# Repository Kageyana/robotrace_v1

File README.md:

# robotrace_v1

# 不具合情報
- リセット時にSDA端子がLOWに固定される.
  
  原因
  
  BNO055が通信中にリセットされBUSY状態になったから

参考

[STM32F1のI2Cの初期化でハマった](http://hima-tubusi.blogspot.com/2016/09/stm32f1i2c.html)

[STM32のI2C初期化で久しぶりにはまった](http://denshikousakusenka.blog.fc2.com/blog-entry-231.html)

[STM32のI2Cペリフェラルの初期化におけるヒント](https://www.stmcu.jp/design/document/technical_note/51180/)

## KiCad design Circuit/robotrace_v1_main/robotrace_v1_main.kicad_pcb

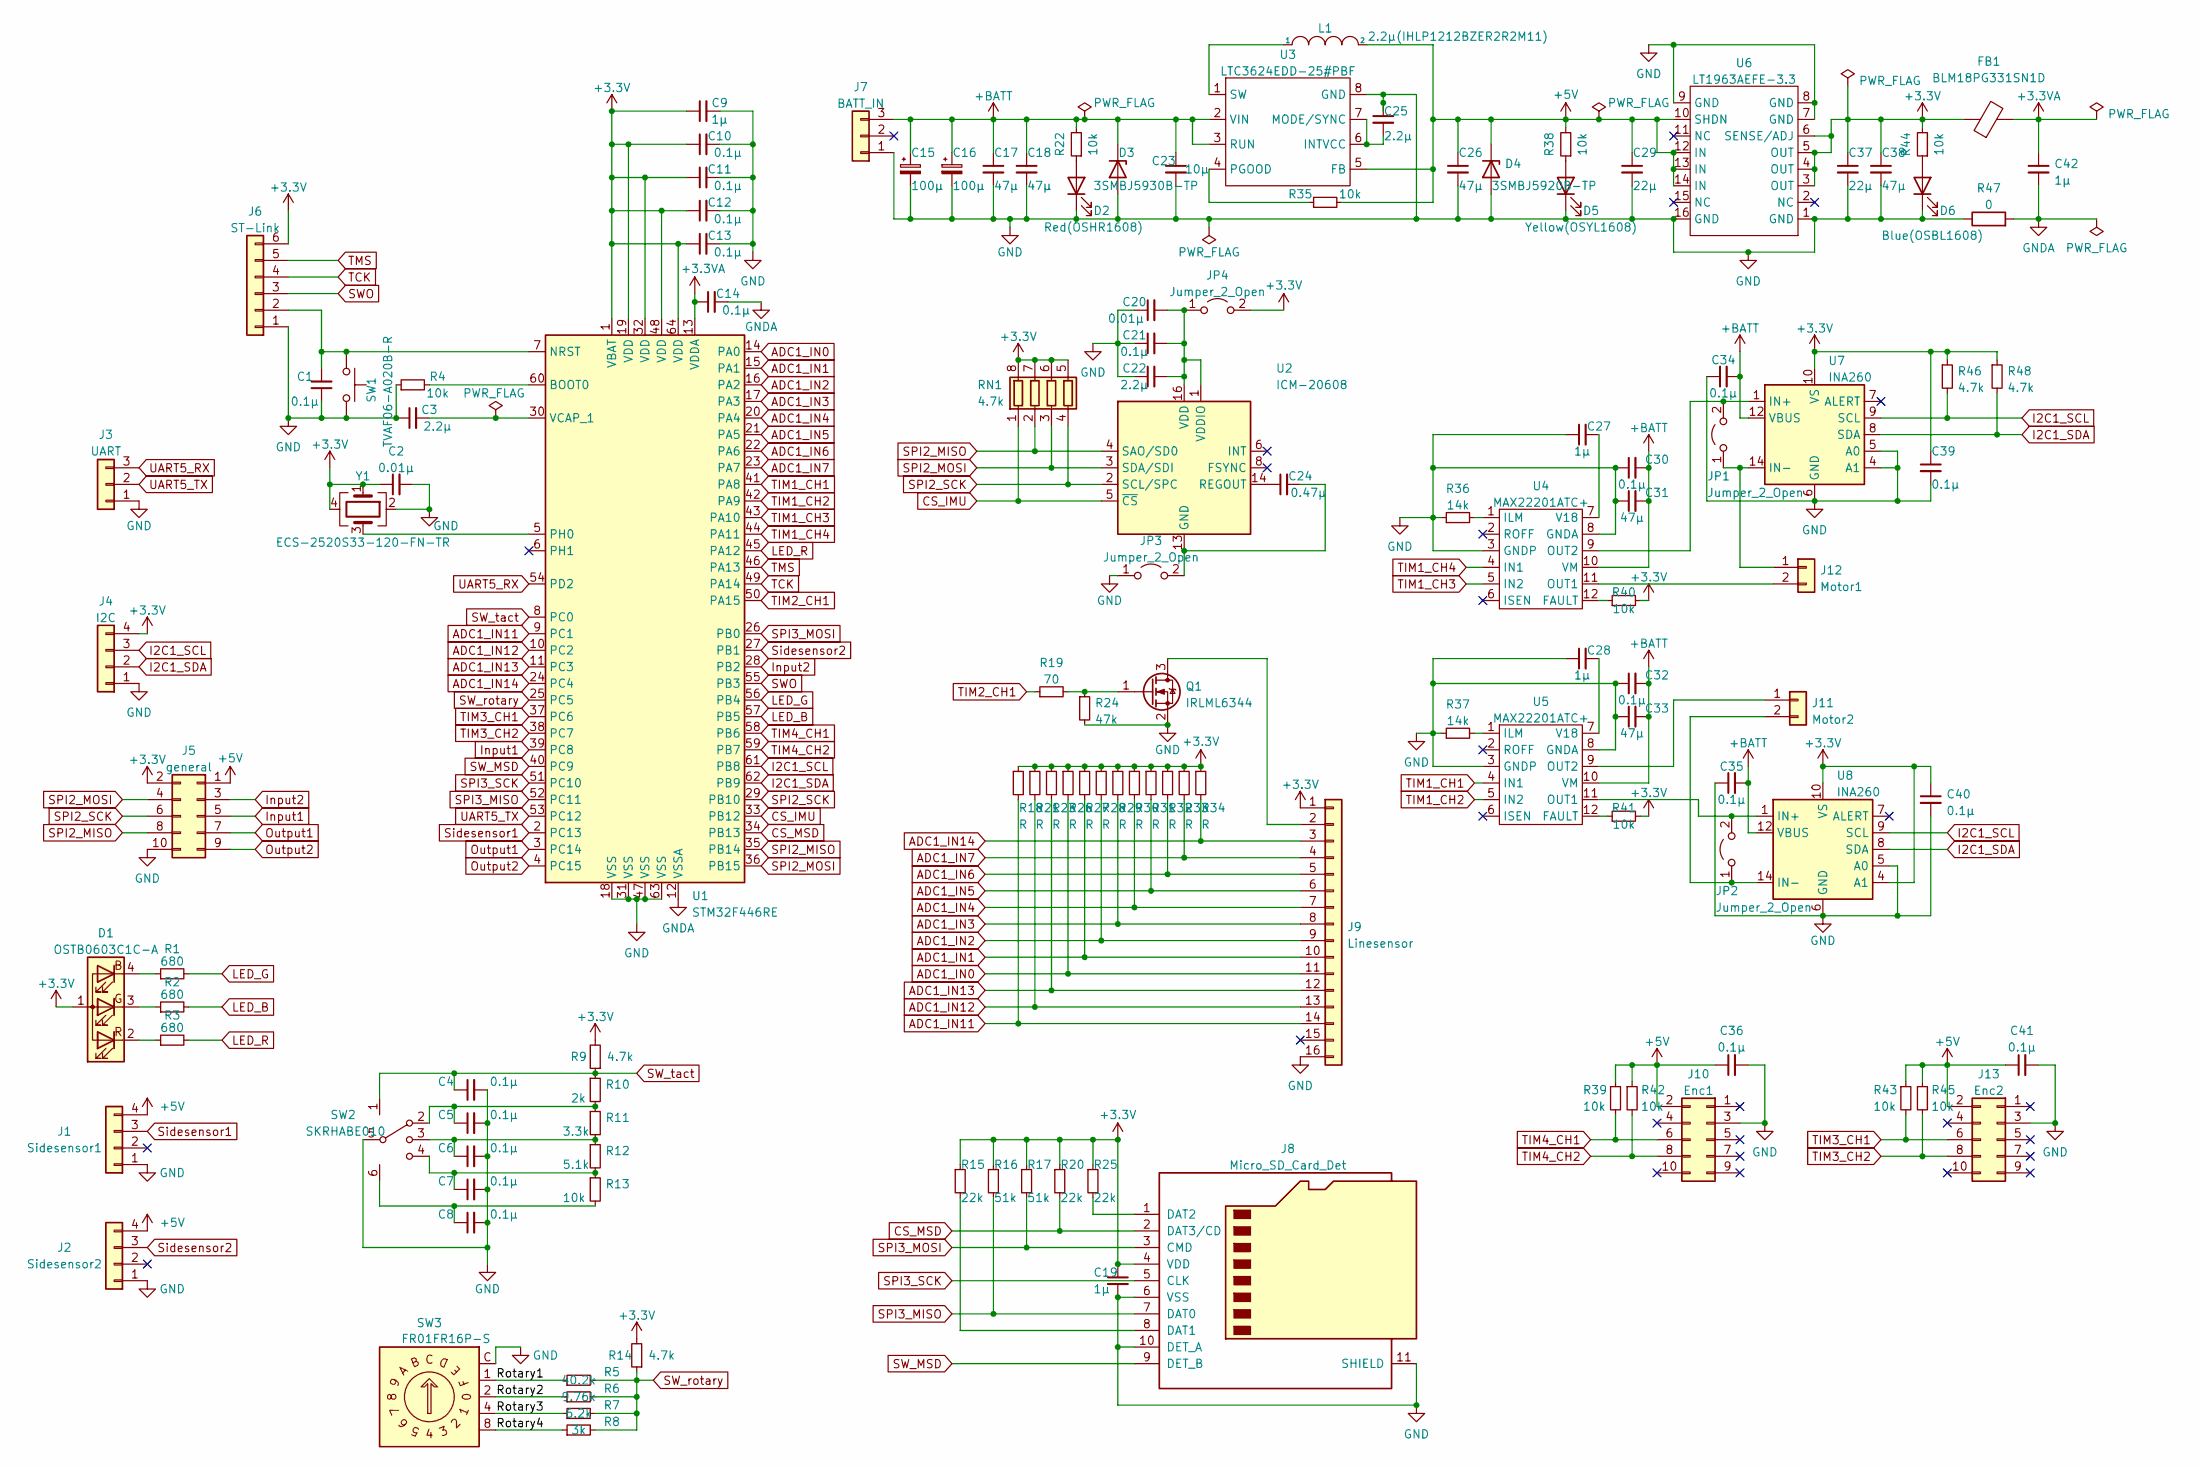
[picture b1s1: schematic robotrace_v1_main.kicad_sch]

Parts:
C1, C4, C5, C6, C7, C8, C10, C11, C12, C13, C14, C21, C30, C32, C34, C35, C36, C39, C40, C41: 0.1μ; C_0402_1005Metric_Pad0.74x0.62mm_HandSolder
C2, C20: 0.01μ; C_0402_1005Metric_Pad0.74x0.62mm_HandSolder
C3, C22, C25: 2.2μ; C_0402_1005Metric_Pad0.74x0.62mm_HandSolder
C9, C19, C27, C28, C42: 1μ; C_0402_1005Metric_Pad0.74x0.62mm_HandSolder
C15, C16: 100μ; CP_Elec_6.3x7.7
C17, C18, C26, C31, C33, C38: 47μ; C_1210_3225Metric_Pad1.33x2.70mm_HandSolder
C23: 10μ; C_0402_1005Metric_Pad0.74x0.62mm_HandSolder
C24: 0.47μ; C_0402_1005Metric_Pad0.74x0.62mm_HandSolder
C29: 22μ; C_0805_2012Metric_Pad1.18x1.45mm_HandSolder
C37: 22μ; C_0402_1005Metric_Pad0.74x0.62mm_HandSolder
D1: OSTB0603C1C-A; LED_Cree-PLCC4_2x2mm_CW
D2: Red(OSHR1608); LED_0603_1608Metric_Pad1.05x0.95mm_HandSolder
D3: 3SMBJ5930B-TP; D_SMA
D4: 3SMBJ5920B-TP; D_SMA
D5: Yellow(OSYL1608); LED_0603_1608Metric_Pad1.05x0.95mm_HandSolder
D6: Blue(OSBL1608); LED_0603_1608Metric_Pad1.05x0.95mm_HandSolder
FB1: BLM18PG331SN1D; D_0603_1608Metric
J1: Sidesensor1; Molex_FFC_1x4-1MP_P0.5mm_Horizontal
J2: Sidesensor2; Molex_FFC_1x4-1MP_P0.5mm_Horizontal
J3: UART; JST_SH_BM03B-SRSS-TB_1x03-1MP_P1.00mm_Vertical
J4: I2C; JST_SH_BM04B-SRSS-TB_1x04-1MP_P1.00mm_Vertical
J5: general; PinSocket_2x05_P1.27mm_Vertical
J6: ST-Link; JST_SH_BM06B-SRSS-TB_1x06-1MP_P1.00mm_Vertical
J7: BATT_IN; Molex_mini-SPOX_1x03_P2.54mm_Vertical
J8: Micro_SD_Card_Det; microSD_HC_Hirose_DM3AT-SF-PEJM5
J9: Linesensor; Molex_1x16_P0.50mm_Horizontal
J10: Enc1; PinSocket_2x05_P1.27mm_Vertical
J11: Motor2; Molex_mini-SPOX_1x02_P2.54mm_Vertical
J12: Motor1; Molex_mini-SPOX_1x02_P2.54mm_Vertical
J13: Enc2; PinSocket_2x05_P1.27mm_Vertical
JP1, JP2, JP3, JP4: Jumper_2_Open; SolderJumper-2_P1.3mm_Open_TrianglePad1.0x1.5mm
L1: 2.2μ(IHLP1212BZER2R2M11); L_Vishay_IHLP-1212
Q1: IRLML6344; SOT-23
R1, R2, R3: 680; R_0603_1608Metric
R4, R13, R22, R35, R38, R39, R40, R41, R42, R43, R44, R45: 10k; R_0603_1608Metric
R5: 40.2k; R_0603_1608Metric
R6: 9.76k; R_0603_1608Metric
R7: 6.2k; R_0603_1608Metric
R8: 3k; R_0603_1608Metric
R9, R14, R46, R48: 4.7k; R_0603_1608Metric
R10: 2k; R_0603_1608Metric
R11: 3.3k; R_0603_1608Metric
R12: 5.1k; R_0603_1608Metric
R15, R20, R25: 22k; R_0603_1608Metric
R16, R17: 51k; R_0603_1608Metric
R18, R21, R23, R26, R27, R28, R29, R30, R31, R32, R33, R34: R; R_0603_1608Metric
R19: 70; R_0603_1608Metric
R24: 47k; R_0603_1608Metric
R36, R37: 14k; R_0603_1608Metric
R47: 0; R_0603_1608Metric
RN1: 4.7k; R_Array_Convex_4x0402
SW1: TVAF06-A020B-R; SW_Push_SPST_NO_Alps_SKRK
SW2: SKRHABE010; SKRHAAE010
SW3: FR01FR16P-S
U1: STM32F446RE; LQFP-64_10x10mm_P0.5mm
U2: ICM-20608; LGA-16_3x3mm_P0.5mm_LayoutBorder3x5y
U3: LTC3624EDD-25#PBF; DFN-8-1EP_3x3mm_P0.5mm_EP1.65x2.38mm
U4, U5: MAX22201ATC+; DFN-12-1EP_3x3mm_P0.5mm_EP1.6x2.5mm
U6: LT1963AEFE-3.3; HTSSOP-16-1EP_4.4x5mm_P0.65mm_EP3.4x5mm
U7, U8: INA260; TSSOP-16_4.4x5mm_P0.65mm
Y1: ECS-2520S33-120-FN-TR; Crystal_SMD_EuroQuartz_MT-4Pin_3.2x2.5mm

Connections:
+3.3VA: C14.1, C42.1, FB1.2, U1.13 (VDDA)
+3V3: C2.1, C9.1, C10.1, C11.1, C12.1, C13.1, C19.1, C37.1, C38.1, C39.1, C40.1, D1.1 (A), FB1.1, J4.4, J5.2, J6.6, J8.4 (VDD), J9.1, JP4.2 (B), R9.2, R14.2, R15.1, R16.1, R17.1, R18.1, R20.1, R21.1, R23.1, R25.1, R26.1, R27.1, R28.1, R29.1, R30.1, R31.1, R32.1, R33.1, R34.1, R40.2, R41.2, R44.2, R46.1, R48.1, RN1.5 (R4.2), RN1.6 (R3.2), RN1.7 (R2.2), RN1.8 (R1.2), U1.1 (VBAT), U1.19 (VDD), U1.32 (VDD), U1.48 (VDD), U1.64 (VDD), U6.3 (OUT), U6.4 (OUT), U6.5 (OUT), U6.6 (SENSE/ADJ), U7.10 (VS), U8.4 (A1), U8.10 (VS), Y1.1, Y1.4
+5V: C26.1, C29.1, C36.1, C41.1, D4.1 (K), J1.4, J2.4, J5.1, J10.2, J13.2, L1.2, R35.2, R38.2, R39.1, R42.1, R43.1, R45.1, U3.5 (FB), U6.10 (SHDN), U6.12 (IN), U6.13 (IN), U6.14 (IN)
+BATT: C15.1, C16.1, C17.1, C18.1, C23.1, C30.2, C31.2, C32.2, C33.2, C34.2, C35.2, D3.1 (K), J7.3, R22.2, U3.2 (VIN), U3.3 (RUN), U4.10 (VM), U5.10 (VM), U7.12 (VBUS), U8.12 (VBUS)
/Rotary1: R5.1, SW3.1
/Rotary2: R6.1, SW3.2
/Rotary3: R7.1, SW3.4
/Rotary4: R8.1, SW3.8
ADC1_IN0: J9.11, R26.2, U1.14 (PA0)
ADC1_IN1: J9.10, R27.2, U1.15 (PA1)
ADC1_IN2: J9.9, R28.2, U1.16 (PA2)
ADC1_IN3: J9.8, R29.2, U1.17 (PA3)
ADC1_IN4: J9.7, R30.2, U1.20 (PA4)
ADC1_IN5: J9.6, R31.2, U1.21 (PA5)
ADC1_IN6: J9.5, R32.2, U1.22 (PA6)
ADC1_IN7: J9.4, R33.2, U1.23 (PA7)
ADC1_IN11: J9.14, R18.2, U1.9 (PC1)
ADC1_IN12: J9.13, R21.2, U1.10 (PC2)
ADC1_IN13: J9.12, R23.2, U1.11 (PC3)
ADC1_IN14: J9.3, R34.2, U1.24 (PC4)
CS_IMU: RN1.1 (R1.1), U1.33 (PB12), U2.5 (~CS)
CS_MSD: J8.2 (DAT3/CD), R20.2, U1.34 (PB13)
GNDA: C14.2, C42.2, R47.2, U1.12 (VSSA)
I2C1_SCL: J4.3, R46.2, U1.61 (PB8), U7.9 (SCL), U8.9 (SCL)
I2C1_SDA: J4.2, R48.2, U1.62 (PB9), U7.8 (SDA), U8.8 (SDA)
Input1: J5.5, U1.39 (PC8)
Input2: J5.3, U1.28 (PB2)
LED1: R1.2, U1.56 (PB4)
LED2: R2.2, U1.57 (PB5)
LED3: R3.2, U1.45 (PA12)
unnamed: C1.2, J6.2, SW1.1, U1.7 (NRST)
unnamed: C3.2, U1.30 (VCAP_1)
unnamed: C5.1, R10.2, R11.1, SW2.2
unnamed: C6.1, R11.2, R12.1, SW2.3
unnamed: C7.1, R12.2, R13.1, SW2.4
unnamed: C20.2, C21.2, C22.2, JP4.1 (A), U2.1 (VDDIO), U2.16 (VDD)
unnamed: C24.1, U2.14 (REGOUT)
unnamed: C24.2, JP3.2 (B), U2.9 (GND), U2.10 (GND), U2.11 (GND), U2.12 (GND), U2.13 (GND), U2.15 (GND)
unnamed: C25.2, U3.6 (INTVCC), U3.7 (MODE/SYNC)
unnamed: C27.2, U4.7 (V18)
unnamed: C28.2, U5.7 (V18)
unnamed: D1.2 (RK), R3.1
unnamed: D1.3 (GK), R2.1
unnamed: D1.4 (BK), R1.1
unnamed: D2.2 (A), R22.1
unnamed: D5.2 (A), R38.1
unnamed: D6.2 (A), R44.1
unnamed: J8.1 (DAT2), R25.2
unnamed: J8.8 (DAT1), R15.2
unnamed: J9.2, Q1.3 (D)
unnamed: J11.1, U5.9 (OUT2)
unnamed: J11.2, JP2.1 (A), U8.14 (IN-), U8.15 (IN-), U8.16 (IN-)
unnamed: J12.1, JP1.1 (A), U7.14 (IN-), U7.15 (IN-), U7.16 (IN-)
unnamed: J12.2, U4.11 (OUT1)
unnamed: JP1.2 (B), U4.9 (OUT2), U7.1 (IN+), U7.2 (IN+), U7.3 (IN+)
unnamed: JP2.2 (B), U5.11 (OUT1), U8.1 (IN+), U8.2 (IN+), U8.3 (IN+)
unnamed: L1.1, U3.1 (SW)
unnamed: Q1.1 (G), R19.2, R24.1
unnamed: R4.2, U1.60 (BOOT0)
unnamed: R35.1, U3.4 (PGOOD)
unnamed: R36.2, U4.1 (ILM)
unnamed: R37.2, U5.1 (ILM)
unnamed: R40.1, U4.12 (FAULT)
unnamed: R41.1, U5.12 (FAULT)
unnamed: U1.5 (PH0), Y1.3
Output1: J5.7, U1.3 (PC14)
Output2: J5.9, U1.4 (PC15)
SPI2_MISO: J5.8, RN1.2 (R2.1), U1.35 (PB14), U2.4 (SAO/SD0)
SPI2_MOSI: J5.4, RN1.3 (R3.1), U1.36 (PB15), U2.3 (SDA/SDI)
SPI2_SCK: J5.6, RN1.4 (R4.1), U1.29 (PB10), U2.2 (SCL/SPC)
SPI3_MISO: J8.7 (DAT0), R16.2, U1.52 (PC11)
SPI3_MOSI: J8.3 (CMD), R17.2, U1.26 (PB0)
SPI3_SCK: J8.5 (CLK), U1.51 (PC10)
SWO: J6.3, U1.55 (PB3)
SW_MSD: J8.9 (DET_B), U1.40 (PC9)
SW_rotary: R5.2, R6.2, R7.2, R8.2, R14.1, U1.25 (PC5)
SW_tact: C4.1, R9.1, R10.1, SW2.1, U1.8 (PC0)
Sidesensor1: J1.3, U1.2 (PC13)
Sidesensor2: J2.3, U1.27 (PB1)
TCK: J6.4, U1.49 (PA14)
TIM1_CH1: U1.41 (PA8), U5.4 (IN1)
TIM1_CH2: U1.42 (PA9), U5.5 (IN2)
TIM1_CH3: U1.43 (PA10), U4.5 (IN2)
TIM1_CH4: U1.44 (PA11), U4.4 (IN1)
TIM2_CH1: R19.1, U1.50 (PA15)
TIM4_CH1: J10.6, R39.2, U1.58 (PB6)
TIM4_CH2: J10.8, R42.2, U1.59 (PB7)
TIM5_CH1: J13.6, R43.2, U1.37 (PC6)
TIM5_CH2: J13.8, R45.2, U1.38 (PC7)
TMS: J6.5, U1.46 (PA13)
UART5_RX: J3.3, U1.54 (PD2)
UART5_TX: J3.2, U1.53 (PC12)

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
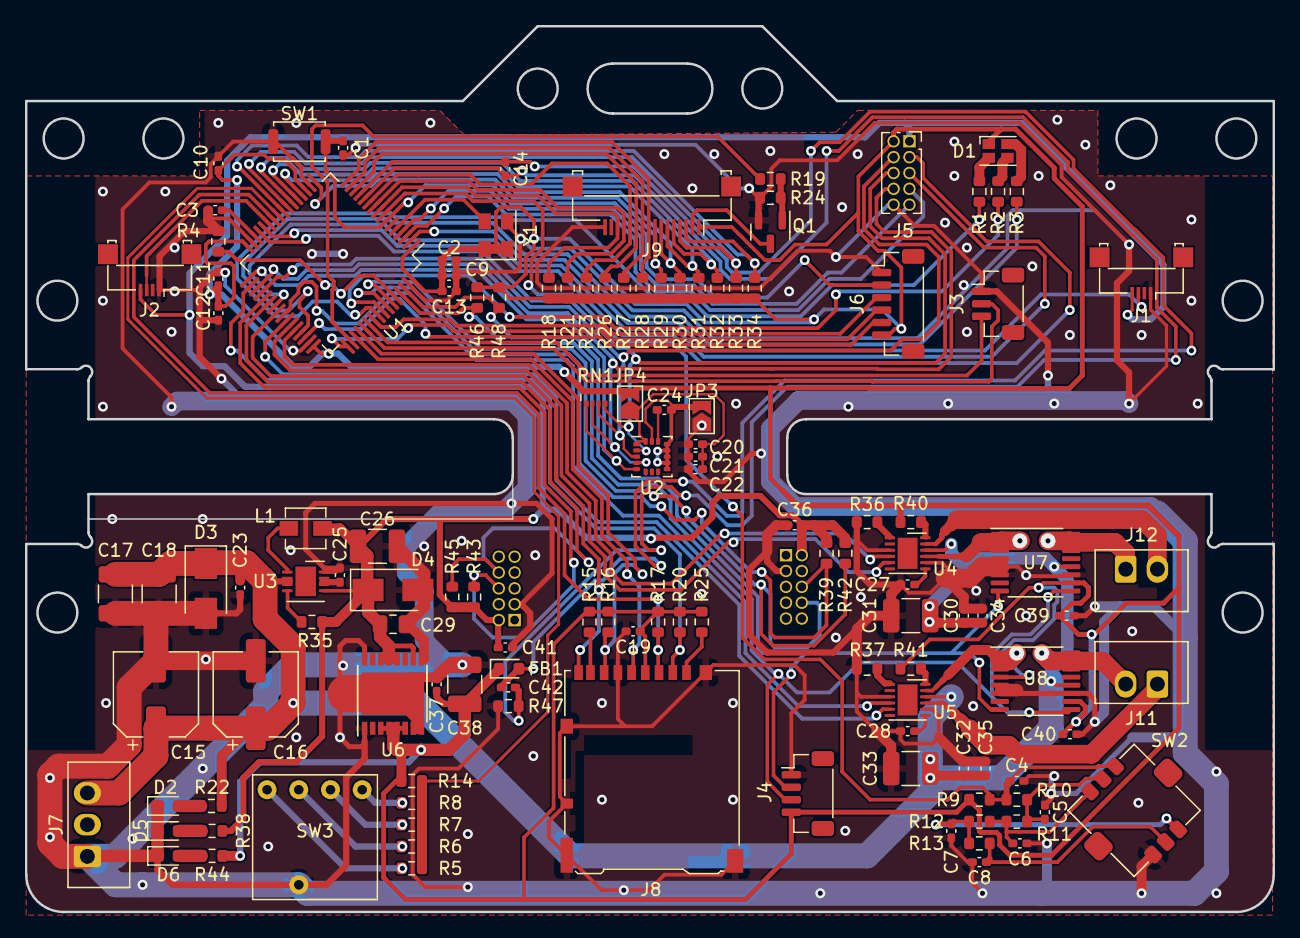
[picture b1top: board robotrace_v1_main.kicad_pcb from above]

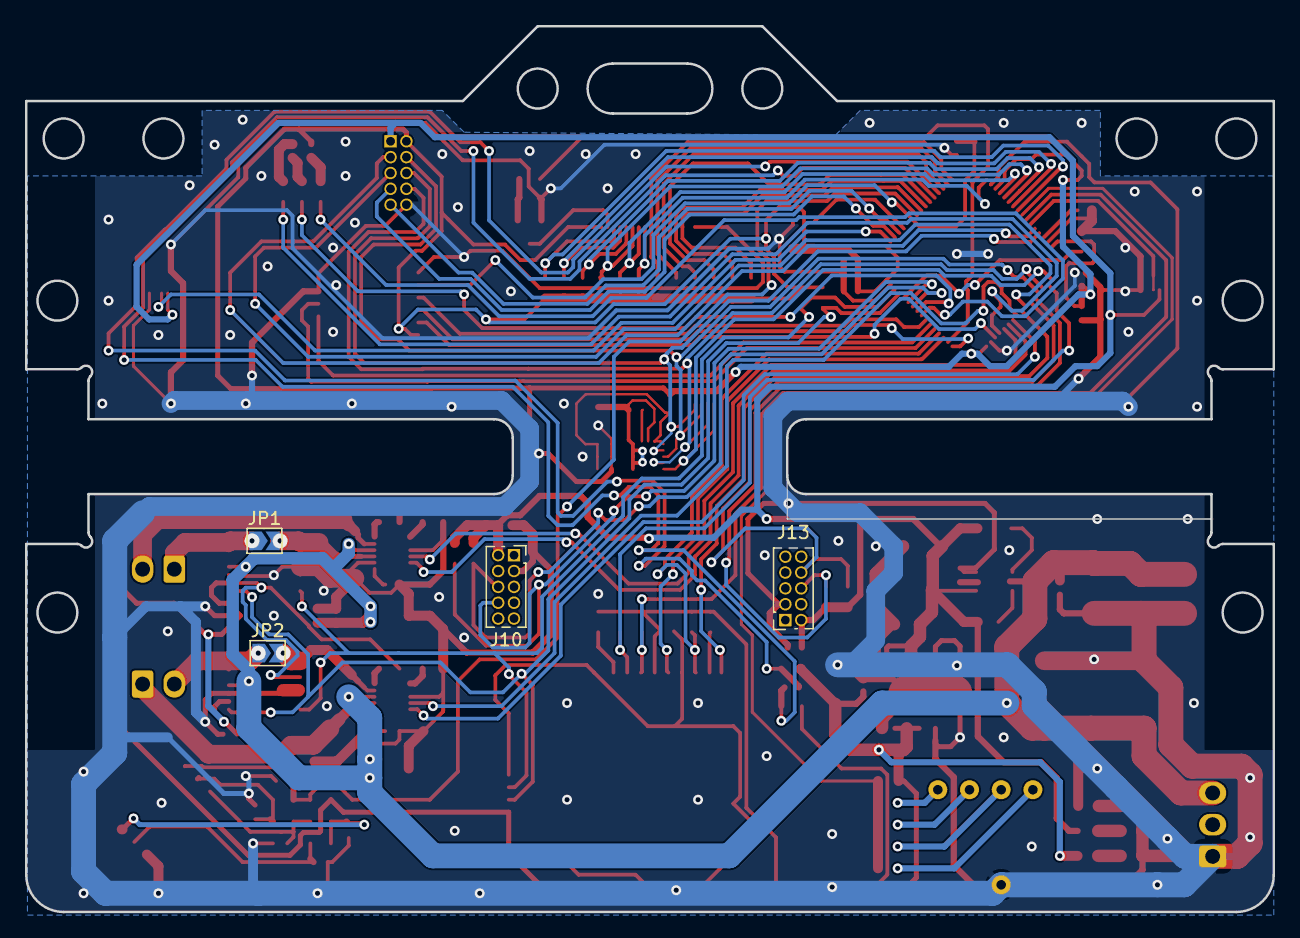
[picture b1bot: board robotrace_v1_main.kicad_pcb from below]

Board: 2 copper layers, 100.0 x 71.0 mm, 129 parts (4 on the bottom side), 94 nets.

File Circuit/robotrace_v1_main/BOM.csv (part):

"Source:","F:\Dropbox\Document\CAD\Ki_cad\robotrace_v1_main\robotrace_v1_main.kicad_sch"
"Date:","2023/03/18 18:05:15"
"Tool:","Eeschema (7.0.0)"
"Generator:","C:\Program Files\KiCad\6.0\bin\scripting\plugins/bom_csv_grouped_by_value_with_fp.py"
"Component Count:","129"
"Ref","Qnty","Value","Cmp name","Footprint","Description","Vendor"
"C1, C4, C5, C6, C7, C8, C10, C11, C12, C13, C14, C21, C30, C32, C34, C35, C36, C39, C40, C41, ","20","0.1μ","C_Small","Capacitor_SMD:C_0402_1005Metric_Pad0.74x0.62mm_HandSolder","Unpolarized capacitor, small symbol",""
"C2, C20, ","2","0.01μ","C_Small","Capacitor_SMD:C_0402_1005Metric_Pad0.74x0.62mm_HandSolder","Unpolarized capacitor, small symbol",""
"C3, C22, C25, ","3","2.2μ","C_Small","Capacitor_SMD:C_0402_1005Metric_Pad0.74x0.62mm_HandSolder","Unpolarized capacitor, small symbol",""
"C9, C19, C27, C28, C42, ","5","1μ","C_Small","Capacitor_SMD:C_0402_1005Metric_Pad0.74x0.62mm_HandSolder","Unpolarized capacitor, small symbol",""
"C15, C16, ","2","100μ","C_Polarized_Small","Capacitor_SMD:CP_Elec_6.3x7.7","Polarized capacitor, small symbol",""
"C17, C18, C26, C31, C33, C38, ","6","47μ","C_Small","Capacitor_SMD:C_1210_3225Metric_Pad1.33x2.70mm_HandSolder","Unpolarized capacitor, small symbol",""
"C23, ","1","10μ","C_Small","Capacitor_SMD:C_0402_1005Metric_Pad0.74x0.62mm_HandSolder","Unpolarized capacitor, small symbol",""
"C24, ","1","0.47μ","C_Small","Capacitor_SMD:C_0402_1005Metric_Pad0.74x0.62mm_HandSolder","Unpolarized capacitor, small symbol",""
"C29, ","1","22μ","C_Small","Capacitor_SMD:C_0805_2012Metric_Pad1.18x1.45mm_HandSolder","Unpolarized capacitor, small symbol",""
"C37, ","1","22μ","C_Small","Capacitor_SMD:C_0402_1005Metric_Pad0.74x0.62mm_HandSolder","Unpolarized capacitor, small symbol",""
"D1, ","1","OSTB0603C1C-A","LED_ARGB","LED_SMD:LED_Cree-PLCC4_2x2mm_CW","RGB LED, anode/red/green/blue",""
"D2, ","1","Red(OSHR1608)","LED","LED_SMD:LED_0603_1608Metric_Pad1.05x0.95mm_HandSolder","Light emitting diode",""
"D3, ","1","3SMBJ5930B-TP","D_Zener","Diode_SMD:D_SMA","Zener diode",""
"D4, ","1","3SMBJ5920B-TP","D_Zener","Diode_SMD:D_SMA","Zener diode",""
"D5, ","1","Yellow(OSYL1608)","LED","LED_SMD:LED_0603_1608Metric_Pad1.05x0.95mm_HandSolder","Light emitting diode",""
"D6, ","1","Blue(OSBL1608)","LED","LED_SMD:LED_0603_1608Metric_Pad1.05x0.95mm_HandSolder","Light emitting diode",""
"FB1, ","1","BLM18PG331SN1D","FerriteBead","Diode_SMD:D_0603_1608Metric","Ferrite bead",""
"J1, ","1","Sidesensor1","Conn_01x04","robot_contest:Molex_FFC_1x4-1MP_P0.5mm_Horizontal","Generic connector, single row, 01x04, script generated (kicad-library-utils/schlib/autogen/connector/)",""
"J2, ","1","Sidesensor2","Conn_01x04","robot_contest:Molex_FFC_1x4-1MP_P0.5mm_Horizontal","Generic connector, single row, 01x04, script generated (kicad-library-utils/schlib/autogen/connector/)",""
"J3, ","1","UART","Conn_01x03","Connector_JST:JST_SH_BM03B-SRSS-TB_1x03-1MP_P1.00mm_Vertical","Generic connector, single row, 01x03, script generated (kicad-library-utils/schlib/autogen/connector/)",""
"J4, ","1","I2C","Conn_01x04","Connector_JST:JST_SH_BM04B-SRSS-TB_1x04-1MP_P1.00mm_Vertical","Generic connector, single row, 01x04, script generated (kicad-library-utils/schlib/autogen/connector/)",""
"J5, ","1","general","Conn_02x05_Odd_Even","Connector_PinSocket_1.27mm:PinSocket_2x05_P1.27mm_Vertical","Generic connector, double row, 02x05, odd/even pin numbering scheme (row 1 odd numbers, row 2 even numbers), script generated (kicad-library-utils/schlib/autogen/connector/)",""
"J6, ","1","ST-Link","Conn_01x06","Connector_JST:JST_SH_BM06B-SRSS-TB_1x06-1MP_P1.00mm_Vertical","Generic connector, single row, 01x06, script generated (kicad-library-utils/schlib/autogen/connector/)",""
"J7, ","1","BATT_IN","Conn_01x03","robot_contest:Molex_mini-SPOX_1x03_P2.54mm_Vertical","Generic connector, single row, 01x03, script generated (kicad-library-utils/schlib/autogen/connector/)",""
"J8, ","1","Micro_SD_Card_Det","Micro_SD_Card_Det","Connector_Card:microSD_HC_Hirose_DM3AT-SF-PEJM5","Micro SD Card Socket with card detection pins",""
"J9, ","1","Linesensor","Conn_01x16","robot_contest:Molex_1x16_P0.50mm_Horizontal","Generic connector, single row, 01x16, script generated (kicad-library-utils/schlib/autogen/connector/)",""
"J10, ","1","Enc1","Conn_02x05_Odd_Even","Connector_PinSocket_1.27mm:PinSocket_2x05_P1.27mm_Vertical","Generic connector, double row, 02x05, odd/even pin numbering scheme (row 1 odd numbers, row 2 even numbers), script generated (kicad-library-utils/schlib/autogen/connector/)",""
"J11, ","1","Motor2","Conn_01x02","robot_contest:Molex_mini-SPOX_1x02_P2.54mm_Vertical","Generic connector, single row, 01x02, script generated (kicad-library-utils/schlib/autogen/connector/)",""
"J12, ","1","Motor1","Conn_01x02","robot_contest:Molex_mini-SPOX_1x02_P2.54mm_Vertical","Generic connector, single row, 01x02, script generated (kicad-library-utils/schlib/autogen/connector/)",""
"J13, ","1","Enc2","Conn_02x05_Odd_Even","Connector_PinSocket_1.27mm:PinSocket_2x05_P1.27mm_Vertical","Generic connector, double row, 02x05, odd/even pin numbering scheme (row 1 odd numbers, row 2 even numbers), script generated (kicad-library-utils/schlib/autogen/connector/)",""
"JP1, JP2, JP3, JP4, ","4","Jumper_2_Open","Jumper_2_Open","Jumper:SolderJumper-2_P1.3mm_Open_TrianglePad1.0x1.5mm","Jumper, 2-pole, open",""
"L1, ","1","2.2μ(IHLP1212BZER2R2M11)","INDUCTOR","Inductor_SMD:L_Vishay_IHLP-1212","Inductor symbol for simulation only",""
"Q1, ","1","IRLML6344","Q_NMOS_GSD","Package_TO_SOT_SMD:SOT-23","N-MOSFET transistor, gate/source/drain",""
"R1, R2, R3, ","3","680","R_Small","Resistor_SMD:R_0603_1608Metric","Resistor, small symbol",""
"R4, R13, R22, R35, R38, R39, R40, R41, R42, R43, R44, R45, ","12","10k","R_Small","Resistor_SMD:R_0603_1608Metric","Resistor, small symbol",""
"R5, ","1","40.2k","R_Small","Resistor_SMD:R_0603_1608Metric","Resistor, small symbol",""
"R6, ","1","9.76k","R_Small","Resistor_SMD:R_0603_1608Metric","Resistor, small symbol",""
"R7, ","1","6.2k","R_Small","Resistor_SMD:R_0603_1608Metric","Resistor, small symbol",""
"R8, ","1","3k","R_Small","Resistor_SMD:R_0603_1608Metric","Resistor, small symbol",""
"R9, R14, R46, R48, ","4","4.7k","R_Small","Resistor_SMD:R_0603_1608Metric","Resistor, small symbol",""
"R10, ","1","2k","R_Small","Resistor_SMD:R_0603_1608Metric","Resistor, small symbol",""
"R11, ","1","3.3k","R_Small","Resistor_SMD:R_0603_1608Metric","Resistor, small symbol",""
"R12, ","1","5.1k","R_Small","Resistor_SMD:R_0603_1608Metric","Resistor, small symbol",""
"R15, R20, R25, ","3","22k","R_Small","Resistor_SMD:R_0603_1608Metric","Resistor, small symbol",""
"R16, R17, ","2","51k","R_Small","Resistor_SMD:R_0603_1608Metric","Resistor, small symbol",""
"R18, R21, R23, R26, R27, R28, R29, R30, R31, R32, R33, R34, ","12","R","R_Small","Resistor_SMD:R_0603_1608Metric","Resistor, small symbol",""
"R19, ","1","70","R_Small","Resistor_SMD:R_0603_1608Metric","Resistor, small symbol",""
"R24, ","1","47k","R_Small","Resistor_SMD:R_0603_1608Metric","Resistor, small symbol",""
"R36, R37, ","2","14k","R_Small","Resistor_SMD:R_0603_1608Metric","Resistor, small symbol",""
"R47, ","1","0","R","Resistor_SMD:R_0603_1608Metric","Resistor",""
"RN1, ","1","4.7k","R_Pack04","Resistor_SMD:R_Array_Convex_4x0402","4 resistor network, parallel topology",""
"SW1, ","1","TVAF06-A020B-R","SW_Push","Button_Switch_SMD:SW_Push_SPST_NO_Alps_SKRK","Push button switch, generic, two pins",""
"SW2, ","1","SKRHABE010","SW_SP3T","robot_contest:SKRHAAE010","Switch, three position, single pole triple throw, 3 position switch, SP3T",""
"SW3, ","1","FR01FR16P-S","SW_Coded_SH-7050","robot_contest:FR01FR16P-S","Rotary switch, 4-bit encoding, 16 positions, Real code",""
"U1, ","1","STM32F446RE","STM32F446RCTx","Package_QFP:LQFP-64_10x10mm_P0.5mm","ARM Cortex-M4 MCU, 256KB flash, 128KB RAM, 180MHz, 1.8-3.6V, 50 GPIO, LQFP-64",""
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
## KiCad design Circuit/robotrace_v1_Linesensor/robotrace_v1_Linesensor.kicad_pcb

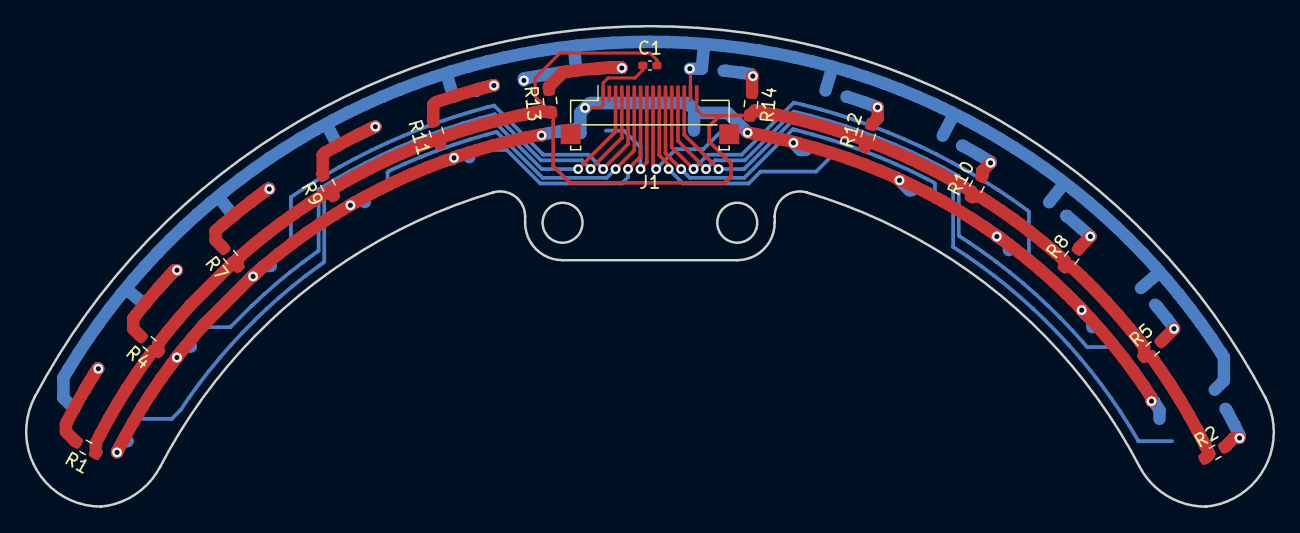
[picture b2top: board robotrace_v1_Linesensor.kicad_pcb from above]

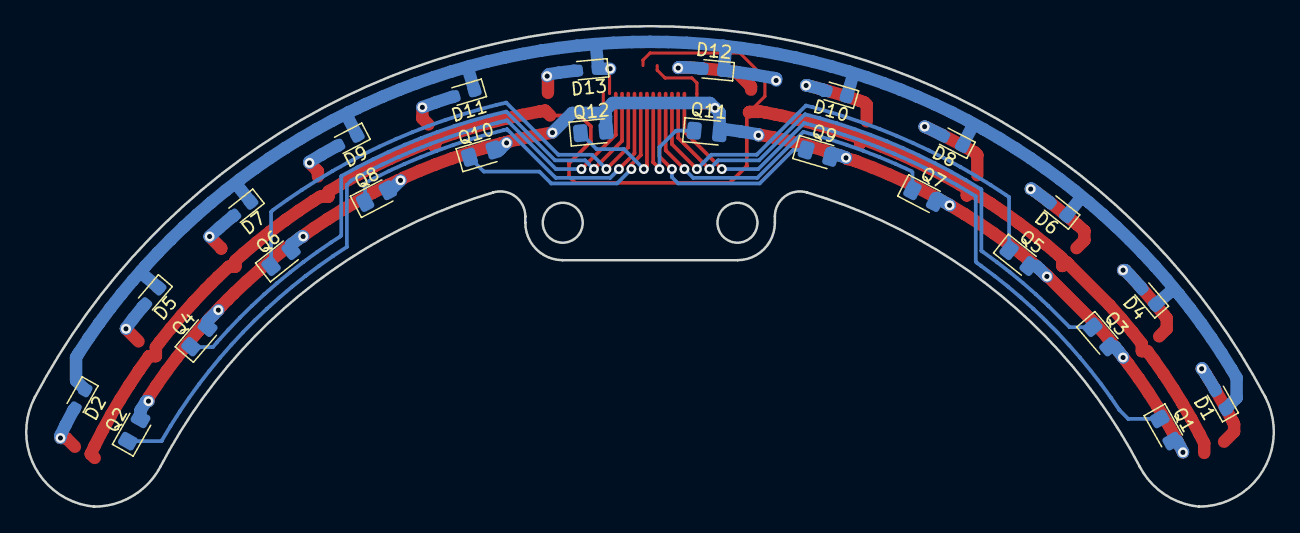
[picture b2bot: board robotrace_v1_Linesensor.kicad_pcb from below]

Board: 2 copper layers, 100.0 x 38.5 mm, 38 parts (24 on the bottom side), 27 nets.

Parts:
C1: 1μ; C_0402_1005Metric_Pad0.74x0.62mm_HandSolder
D1, D2, D4, D5, D6, D7, D8, D9, D10, D11, D12, D13: SIR19-21C/TR8; LED_0603_1608Metric_Pad1.05x0.95mm_HandSolder
J1: FFC_16P; Molex_1x16_P0.50mm_Horizontal
Q1, Q2, Q3, Q4, Q5, Q6, Q7, Q8, Q9, Q10, Q11, Q12: TEMT7100X01; LED_0805_2012Metric_Pad1.15x1.40mm_HandSolder
R1, R2, R4, R5, R7, R8, R9, R10, R11, R12, R13, R14: 100; R_0603_1608Metric_Pad0.98x0.95mm_HandSolder

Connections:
+3V3: C1.1, J1.16, R1.1, R2.1, R4.1, R5.1, R7.1, R8.1, R9.1, R10.1, R11.1, R12.1, R13.1, R14.1
GND1: C1.2, J1.1, Q1.2 (E), Q2.2 (E), Q3.2 (E), Q4.2 (E), Q5.2 (E), Q6.2 (E), Q7.2 (E), Q8.2 (E), Q9.2 (E), Q10.2 (E), Q11.2 (E), Q12.2 (E)
unnamed: D1.1 (K), D2.1 (K), D4.1 (K), D5.1 (K), D6.1 (K), D7.1 (K), D8.1 (K), D9.1 (K), D10.1 (K), D11.1 (K), D12.1 (K), D13.1 (K), J1.15
unnamed: D1.2 (A), R1.2
unnamed: D2.2 (A), R2.2
unnamed: D4.2 (A), R4.2
unnamed: D5.2 (A), R5.2
unnamed: D6.2 (A), R7.2
unnamed: D7.2 (A), R8.2
unnamed: D8.2 (A), R9.2
unnamed: D9.2 (A), R10.2
unnamed: D10.2 (A), R11.2
unnamed: D11.2 (A), R12.2
unnamed: D12.2 (A), R13.2
unnamed: D13.2 (A), R14.2
unnamed: J1.3, Q1.1 (C)
unnamed: J1.4, Q3.1 (C)
unnamed: J1.5, Q5.1 (C)
unnamed: J1.6, Q7.1 (C)
unnamed: J1.7, Q9.1 (C)
unnamed: J1.8, Q11.1 (C)
unnamed: J1.9, Q12.1 (C)
unnamed: J1.10, Q10.1 (C)
unnamed: J1.11, Q8.1 (C)
unnamed: J1.12, Q6.1 (C)
unnamed: J1.13, Q4.1 (C)
unnamed: J1.14, Q2.1 (C)

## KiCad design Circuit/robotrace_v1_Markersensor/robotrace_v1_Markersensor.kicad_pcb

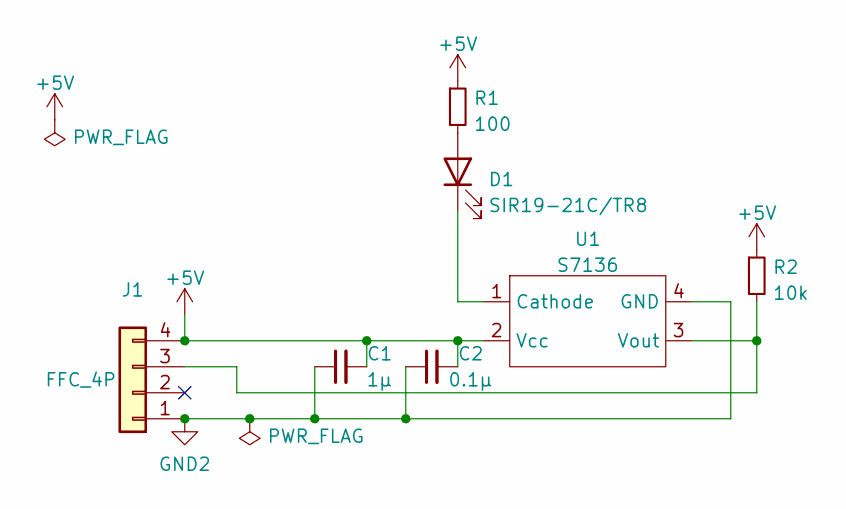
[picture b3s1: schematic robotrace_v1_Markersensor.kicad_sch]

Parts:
C1: 1μ; C_0402_1005Metric_Pad0.74x0.62mm_HandSolder
C2: 0.1μ; C_0402_1005Metric_Pad0.74x0.62mm_HandSolder
D1: SIR19-21C/TR8; LED_0603_1608Metric_Pad1.05x0.95mm_HandSolder
J1: FFC_4P; Molex_FFC_1x4-1MP_P0.5mm_Horizontal
R1: 100; R_0603_1608Metric_Pad0.98x0.95mm_HandSolder
R2: 10k; R_0603_1608Metric_Pad0.98x0.95mm_HandSolder
U1: S7136

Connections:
+5V: C1.2, C2.2, J1.4, R1.1, R2.1, U1.2 (Vcc)
GND2: C1.1, C2.1, J1.1, U1.4 (GND)
unnamed: D1.1 (K), U1.1 (Cathode)
unnamed: D1.2 (A), R1.2
unnamed: J1.3, R2.2, U1.3 (Vout)

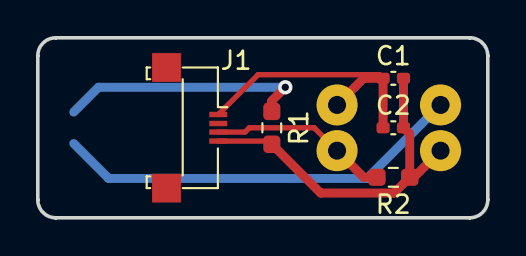
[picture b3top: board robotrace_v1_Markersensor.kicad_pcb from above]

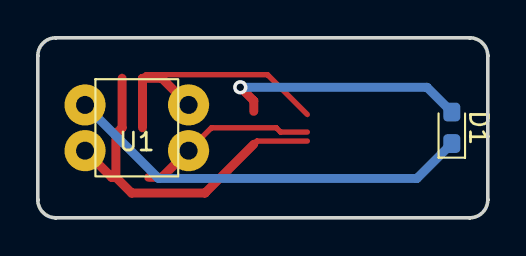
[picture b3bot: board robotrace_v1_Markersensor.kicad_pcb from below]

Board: 2 copper layers, 25.0 x 10.0 mm, 7 parts (2 on the bottom side), 5 nets.

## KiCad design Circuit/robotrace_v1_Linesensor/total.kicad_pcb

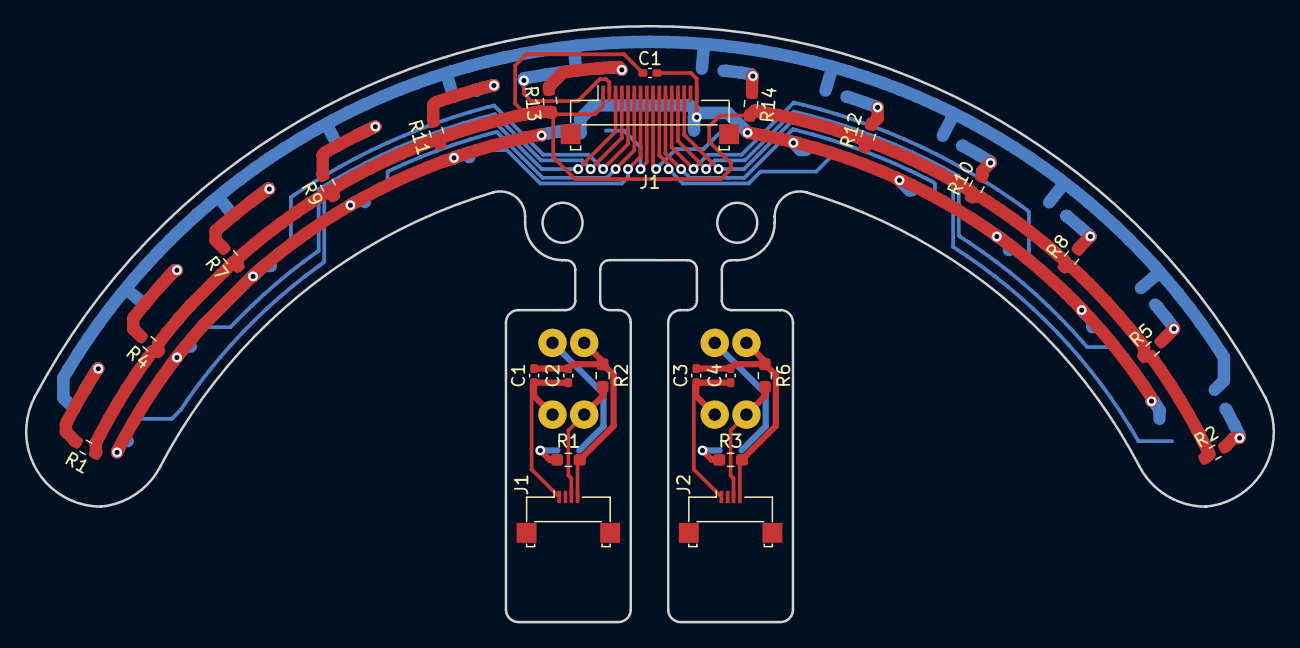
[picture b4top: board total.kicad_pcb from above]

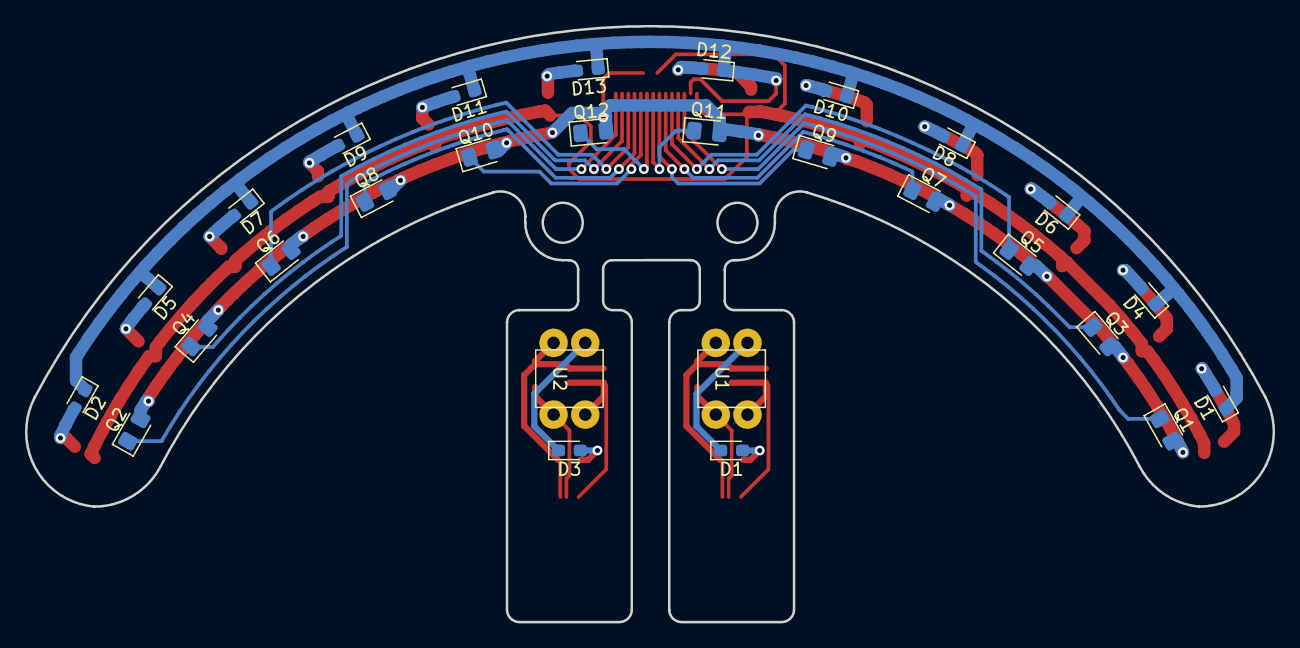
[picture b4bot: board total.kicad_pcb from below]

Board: 2 copper layers, 100.0 x 47.7 mm, 52 parts (28 on the bottom side), 29 nets.

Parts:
C1, C1#2, C3: 1μ; C_0402_1005Metric_Pad0.74x0.62mm_HandSolder
C2, C4: 0.1μ; C_0402_1005Metric_Pad0.74x0.62mm_HandSolder
D1, D1#2, D2, D3, D4, D5, D6, D7, D8, D9, D10, D11, D12, D13: SIR19-21C/TR8; LED_0603_1608Metric_Pad1.05x0.95mm_HandSolder
J1, J2: FFC_4P; Molex_FFC_1x4-1MP_P0.5mm_Horizontal
J1#2: FFC_16P; Molex_1x16_P0.50mm_Horizontal
Q1, Q2, Q3, Q4, Q5, Q6, Q7, Q8, Q9, Q10, Q11, Q12: TEMT7100X01; LED_0805_2012Metric_Pad1.15x1.40mm_HandSolder
R1, R1#2, R2#2, R3, R4, R5, R7, R8, R9, R10, R11, R12, R13, R14: 100; R_0603_1608Metric_Pad0.98x0.95mm_HandSolder
R2, R6: 10k; R_0603_1608Metric_Pad0.98x0.95mm_HandSolder
U1, U2: S7136

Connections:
+3V3: C1#2.1, J1#2.1, R1#2.1, R2#2.1, R4.1, R5.1, R7.1, R8.1, R9.1, R10.1, R11.1, R12.1, R13.1, R14.1
+5V: C1.2, C2.2, C3.2, C4.2, J1.4, J2.4, R1.1, R2.1, R3.1, R6.1, U1.2 (Vcc), U2.2 (Vcc)
GND1: C1#2.2, J1#2.16, Q1.2 (E), Q2.2 (E), Q3.2 (E), Q4.2 (E), Q5.2 (E), Q6.2 (E), Q7.2 (E), Q8.2 (E), Q9.2 (E), Q10.2 (E), Q11.2 (E), Q12.2 (E)
GND2: C1.1, C2.1, C3.1, C4.1, J1.1, J2.1, U1.4 (GND), U2.4 (GND)
unnamed: D1.1 (K), D1#2.1 (K), D2.1 (K), D3.1 (K), D4.1 (K), D5.1 (K), D6.1 (K), D7.1 (K), D8.1 (K), D9.1 (K), D10.1 (K), D11.1 (K), D12.1 (K), D13.1 (K), J1#2.2, U1.1 (Cathode), U2.1 (Cathode)
unnamed: D1.2 (A), D1#2.2 (A), D3.2 (A), R1.2, R1#2.2, R3.2
unnamed: D2.2 (A), R2#2.2
unnamed: D4.2 (A), R4.2
unnamed: D5.2 (A), R5.2
unnamed: D6.2 (A), R7.2
unnamed: D7.2 (A), R8.2
unnamed: D8.2 (A), R9.2
unnamed: D9.2 (A), R10.2
unnamed: D10.2 (A), R11.2
unnamed: D11.2 (A), R12.2
unnamed: D12.2 (A), R13.2
unnamed: D13.2 (A), R14.2
unnamed: J1.3, J1#2.3, J2.3, Q1.1 (C), R2.2, R6.2, U1.3 (Vout), U2.3 (Vout)
unnamed: J1#2.4, Q3.1 (C)
unnamed: J1#2.5, Q5.1 (C)
unnamed: J1#2.6, Q7.1 (C)
unnamed: J1#2.7, Q9.1 (C)
unnamed: J1#2.8, Q11.1 (C)
unnamed: J1#2.9, Q12.1 (C)
unnamed: J1#2.10, Q10.1 (C)
unnamed: J1#2.11, Q8.1 (C)
unnamed: J1#2.12, Q6.1 (C)
unnamed: J1#2.13, Q4.1 (C)
unnamed: J1#2.14, Q2.1 (C)

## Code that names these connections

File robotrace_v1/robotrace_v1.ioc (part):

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Mcu.Name=STM32F446R(C-E)Tx
Mcu.Package=LQFP64
Mcu.UserName=STM32F446RETx
PA0-WKUP.Signal=ADCx_IN0
PA1.Signal=ADCx_IN1
PA10.Signal=S_TIM1_CH3
PA11.Signal=S_TIM1_CH4
PA12.GPIOParameters=PinState,GPIO_PuPd,GPIO_Label
PA12.GPIO_Label=LED_R
PA12.GPIO_PuPd=GPIO_PULLUP
PA12.PinState=GPIO_PIN_SET
PA12.Signal=GPIO_Output
PA13.GPIOParameters=GPIO_Label
PA13.GPIO_Label=TMS
PA13.Mode=Trace_Asynchronous_SW
PA13.Signal=SYS_JTMS-SWDIO
PA14.GPIOParameters=GPIO_Label
PA14.GPIO_Label=TCK
PA14.Mode=Trace_Asynchronous_SW
PA14.Signal=SYS_JTCK-SWCLK
PA15.Signal=S_TIM2_CH1_ETR
PA2.Signal=ADCx_IN2
PA3.Signal=ADCx_IN3
PA4.Signal=ADCx_IN4
PA5.Signal=ADCx_IN5
PA6.Signal=ADCx_IN6
PA7.Signal=ADCx_IN7
PA8.Signal=S_TIM1_CH1
PA9.Signal=S_TIM1_CH2
PB0.Mode=Full_Duplex_Master
PB0.Signal=SPI3_MOSI
PB1.GPIOParameters=GPIO_PuPd,GPIO_Label
PB1.GPIO_Label=Sidesensor2
PB1.GPIO_PuPd=GPIO_PULLUP
PB1.Signal=GPIO_Input
PB10.Mode=Full_Duplex_Master
PB10.Signal=SPI2_SCK
PB12.GPIOParameters=PinState,GPIO_PuPd,GPIO_Label
PB12.GPIO_Label=CS_IMU
PB12.GPIO_PuPd=GPIO_PULLUP
PB12.PinState=GPIO_PIN_SET
PB12.Signal=GPIO_Output
PB13.GPIOParameters=PinState,GPIO_PuPd,GPIO_Label
PB13.GPIO_Label=CS_MSD
PB13.GPIO_PuPd=GPIO_PULLUP
PB13.PinState=GPIO_PIN_SET
PB13.Signal=GPIO_Output
PB14.Mode=Full_Duplex_Master
PB14.Signal=SPI2_MISO
PB15.Mode=Full_Duplex_Master
PB15.Signal=SPI2_MOSI
PB2.GPIOParameters=GPIO_Label
PB2.GPIO_Label=Input2
PB2.Signal=GPIO_Input
PB3.GPIOParameters=GPIO_Label
PB3.GPIO_Label=SWO
PB3.Mode=Trace_Asynchronous_SW
PB3.Signal=SYS_JTDO-SWO
PB4.GPIOParameters=PinState,GPIO_PuPd,GPIO_Label
PB4.GPIO_Label=LED_G
PB4.GPIO_PuPd=GPIO_PULLUP
PB4.PinState=GPIO_PIN_SET
PB4.Signal=GPIO_Output
PB5.GPIOParameters=PinState,GPIO_PuPd,GPIO_Label
PB5.GPIO_Label=LED_B
PB5.GPIO_PuPd=GPIO_PULLUP
PB5.PinState=GPIO_PIN_SET
PB5.Signal=GPIO_Output
PB6.Signal=S_TIM4_CH1
PB7.Signal=S_TIM4_CH2
PB8.Mode=I2C
PB8.Signal=I2C1_SCL
PB9.Mode=I2C
PB9.Signal=I2C1_SDA
PC0.Signal=ADCx_IN10
PC1.Signal=ADCx_IN11
PC10.Mode=Full_Duplex_Master
PC10.Signal=SPI3_SCK
PC11.Mode=Full_Duplex_Master
PC11.Signal=SPI3_MISO
PC12.Mode=Asynchronous
PC12.Signal=UART5_TX
PC13.GPIOParameters=GPIO_PuPd,GPIO_Label
PC13.GPIO_Label=Sidesensor1
PC13.GPIO_PuPd=GPIO_PULLUP
PC13.Signal=GPIO_Input
PC14-OSC32_IN.GPIOParameters=GPIO_PuPd,GPIO_Label
PC14-OSC32_IN.GPIO_Label=Output1
PC14-OSC32_IN.GPIO_PuPd=GPIO_PULLUP
PC14-OSC32_IN.Signal=GPIO_Output
PC15-OSC32_OUT.GPIOParameters=GPIO_PuPd,GPIO_Label
PC15-OSC32_OUT.GPIO_Label=Output2
PC15-OSC32_OUT.GPIO_PuPd=GPIO_PULLUP
PC15-OSC32_OUT.Signal=GPIO_Output
PC2.Signal=ADCx_IN12
PC3.Signal=ADCx_IN13
PC4.Signal=ADCx_IN14
PC5.Signal=ADCx_IN15
PC6.Signal=S_TIM3_CH1
PC7.Signal=S_TIM3_CH2
PC8.GPIOParameters=GPIO_PuPd,GPIO_Label
PC8.GPIO_Label=Input1
PC8.GPIO_PuPd=GPIO_PULLUP
PC8.Signal=GPIO_Input
PC9.GPIOParameters=GPIO_PuPd,GPIO_Label
PC9.GPIO_Label=SW_MSD
PC9.GPIO_PuPd=GPIO_PULLUP
PC9.Signal=GPIO_Input
PD2.Mode=Asynchronous
PD2.Signal=UART5_RX
PH0-OSC_IN.Mode=HSE-External-Oscillator
PH0-OSC_IN.Signal=RCC_OSC_IN
PH1-OSC_OUT.Mode=HSE-External-Oscillator
PH1-OSC_OUT.Signal=RCC_OSC_OUT
RCC.HSE_VALUE=12000000
RCC.SYSCLKFreq_VALUE=180000000
RCC.SYSCLKSource=RCC_SYSCLKSOURCE_PLLCLK
board=NUCLEO-F446RE
boardIOC=true

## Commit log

2022-09-07 init
2022-09-07 LCDが動いた
2022-09-17 ラインセンサの動作を確認した
2022-09-23 0.4m/sでトレースできた
2022-09-25 ゴールマーカーを検出して1周で止まった
2022-09-30 0.8m/sで走った
2022-10-02 0.6m/sでベンチマークコースを完走した
2022-10-03 クロスラインの読み飛ばし処理が動いた
2022-10-30 電流センサ(INA260)が動いた
2022-11-21 MicroSDカードにFAT32形式で書き込めた
2022-11-23 ログが取れるようになった
2022-11-23 gitignoreを追加
2022-11-26 走行ログを取れた
2022-11-27 緊急停止処理を追加
2022-11-27 マーカー検知できた？
2022-12-03 マーカー検出アルゴリズムの改良
2022-12-03 コメントを翻訳した
2022-12-04 ログの保存を小分けにするようにした
2022-12-06 角度制御を追加
2022-12-06 FPUを有効化した
2022-12-10 マーカー検知改善
2022-12-10 microSDの挿入状況をフラグで管理するようにした
2022-12-18 コードを整理した
2023-01-01 起動時にMSDの挿入状況によってLEDの発光パターンを変えるようにした
2023-01-20 ライントレースの制御量を優先するようにした
2023-01-21 コード短縮
2023-02-05 角速度の単位をrad/sに変更した
2023-02-11 しきい値を[rad/s]に変更した
2023-02-11 SDカード関係の関数を外部ファイル化した
2023-02-11 コメントを追加
2023-02-16 マーカー区間ごとに曲率半径を算出できるようにした
2023-02-17 変数名変更
2023-02-17 2次走行用の機能を実装した
2023-02-18 全日本マイクロマウス大会2022試走日に走った
2023-02-20 2次走行用パラメータを調整できるようにした
2023-02-23 通信デバイスの初期化状況をフラグで管理するようにした
2023-02-24 マーカー誤検出処理を追加
2023-02-24 緊急停止処理を外部ファイル化した
2023-02-24 セットアップ画面、走行終了画面を変更した
2023-02-25 リセット時にSDAがlowに固定される問題を修正した
2023-02-25 パラメータ変数を構造体に変更した
2023-02-25 コードの可読性向上
2023-02-25 ジャイロ関係の変数を構造体に変更した
2023-02-25 インクルードパスを追加してエラー表示をなくした
2023-03-03 不要な処理を削除
2023-03-03 定義を変更
2023-03-12 コース記憶関数製作中
2023-03-18 PWMのDuty比指定をCounter Periodが最大値になるように変更した
2023-03-23 PWMのDuty比を0～counterperiodまで調整するようにした
2023-04-08 距離基準の記録走行ができた
2023-04-08 キャリブレーションをしないとスタートできないようにした
2023-04-09 クロスラインの通過時のブレを軽減した
2023-04-11 変数名を変更
2023-08-02 PIDパラメータを調整
2023-08-02 電気回路図を追加
